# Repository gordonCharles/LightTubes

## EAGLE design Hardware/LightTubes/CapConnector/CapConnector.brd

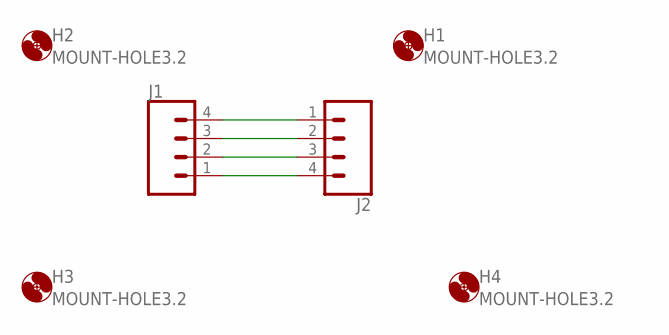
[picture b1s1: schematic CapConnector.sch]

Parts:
H1, H2, H3, H4: MOUNT-HOLE3.2; 3,2
J1: CONN_04POLAR; MOLEX-1X4
J2: CONN_04SMD_LONG; 1X04_SMD_LONG

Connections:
unnamed: J1.4, J2.1
unnamed: J1.3, J2.2
unnamed: J1.2, J2.3
unnamed: J1.1, J2.4

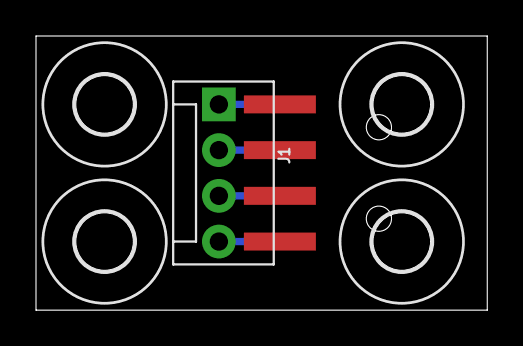
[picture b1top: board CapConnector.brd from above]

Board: 2 copper layers, 25.1 x 15.2 mm, 6 parts (0 on the bottom side), 4 nets.

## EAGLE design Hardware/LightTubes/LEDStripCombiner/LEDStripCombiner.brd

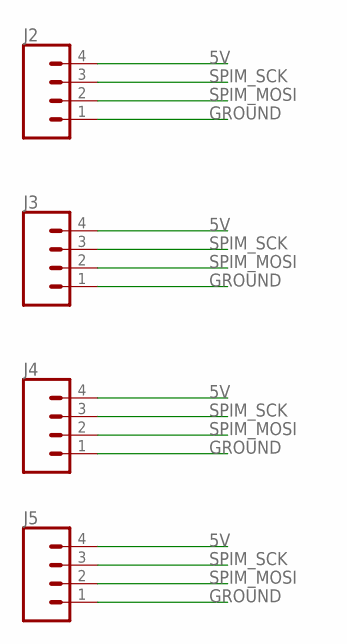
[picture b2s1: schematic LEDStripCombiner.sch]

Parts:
J2, J3, J4, J5: CONN_041X04_NO_SILK; 1X04_NO_SILK

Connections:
5V: J2.4, J3.4, J4.4, J5.4
GROUND: J2.1, J3.1, J4.1, J5.1
SPIM_MOSI: J2.2, J3.2, J4.2, J5.2
SPIM_SCK: J2.3, J3.3, J4.3, J5.3

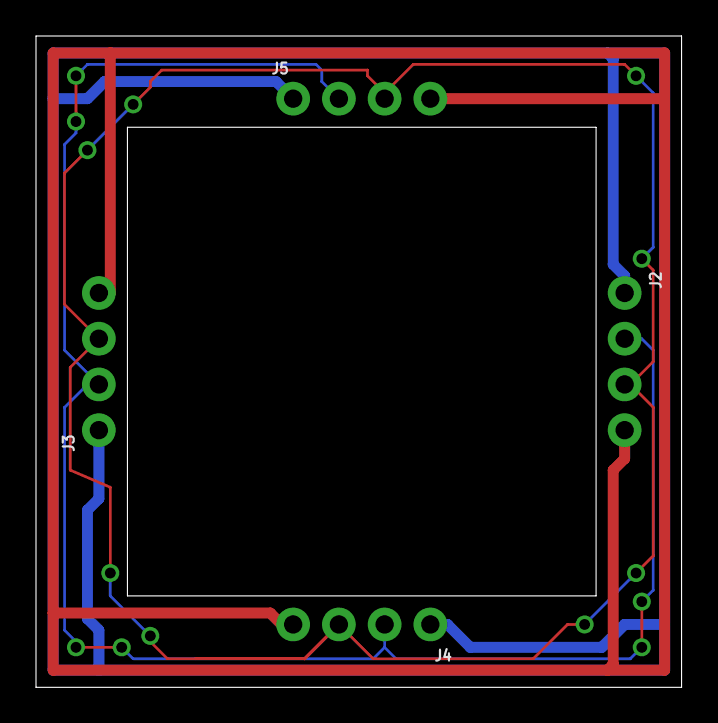
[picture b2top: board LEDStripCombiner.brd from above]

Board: 2 copper layers, 35.9 x 36.2 mm, 4 parts (0 on the bottom side), 4 nets.

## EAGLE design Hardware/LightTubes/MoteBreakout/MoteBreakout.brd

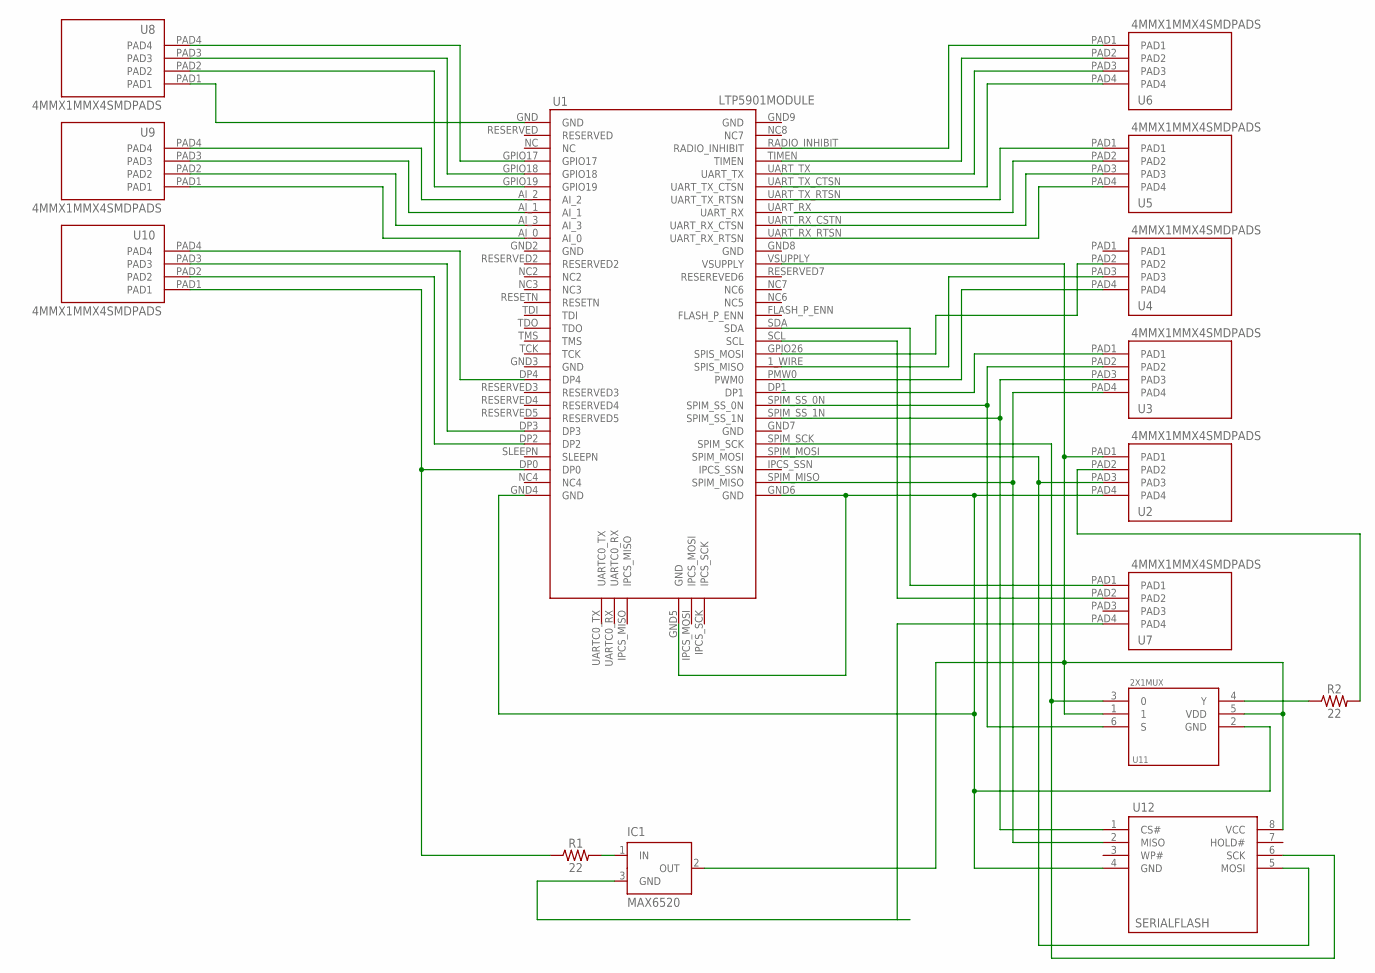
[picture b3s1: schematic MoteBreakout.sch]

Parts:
IC1: MAX6520; SOT23
R1, R2: 22; 0603
U1: LTP5901MODULE; LTP5901
U2, U3, U4, U5, U6, U7, U8, U9, U10: 4MMX1MMX4SMDPADS; 4MMX1MMX4SMD
U11: 2X1MUX; SOT457
U12: SERIALFLASH; 8S2

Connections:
GND: U1.GND2 (GND), U1.GND3 (GND), U1.GND7 (GND), U1.GND8 (GND), U1.GND9 (GND)
unnamed: U1.GND4 (GND), U1.GND5 (GND), U1.GND6 (GND), U2.PAD4, U11.2 (GND), U12.4 (GND)
unnamed: U1.SPIM_MOSI, U2.PAD3, U12.5 (MOSI)
unnamed: U1.SPIM_SCK, U11.3 (0), U12.6 (SCK)
unnamed: IC1.2 (OUT), U1.VSUPPLY, U2.PAD1, U11.1, U11.5 (VDD), U12.8 (VCC)
unnamed: U1.SPIM_MISO, U3.PAD4, U12.2 (MISO)
unnamed: U1.SPIM_SS_1N, U3.PAD3, U12.1 (CS#)
unnamed: U1.SPIM_SS_0N, U3.PAD2, U11.6 (S)
unnamed: U1.DP1, U3.PAD1
unnamed: U1.PMW0 (PWM0), U4.PAD4
unnamed: U1.1_WIRE (SPIS_MISO), U4.PAD3
unnamed: U1.GPIO26 (SPIS_MOSI), U4.PAD2
unnamed: U1.UART_RX_RTSN, U5.PAD4
unnamed: U1.UART_RX_CSTN (UART_RX_CTSN), U5.PAD3
unnamed: U1.UART_TX_RTSN, U5.PAD1
unnamed: U1.UART_TX_CTSN, U6.PAD4
unnamed: U1.UART_TX, U6.PAD3
unnamed: U1.TIMEN, U6.PAD2
unnamed: U1.RADIO_INHIBIT, U6.PAD1
unnamed: U1.GND, U8.PAD1
unnamed: U1.SDA, U7.PAD1
unnamed: U1.SCL, U7.PAD2
unnamed: IC1.3 (GND), U7.PAD4
unnamed: U1.GPIO17, U8.PAD4
unnamed: U1.GPIO18, U8.PAD3
unnamed: U1.GPIO19, U8.PAD2
unnamed: U1.AI_2, U9.PAD4
unnamed: U1.AI_1, U9.PAD3
unnamed: U1.AI_3, U9.PAD2
unnamed: U1.AI_0, U9.PAD1
unnamed: U1.DP4, U10.PAD4
unnamed: U1.DP3, U10.PAD3
unnamed: U1.DP2, U10.PAD2
unnamed: R1.1, U1.DP0, U10.PAD1
unnamed: R2.2, U2.PAD2
unnamed: R2.1, U11.4 (Y)
unnamed: IC1.1 (IN), R1.2

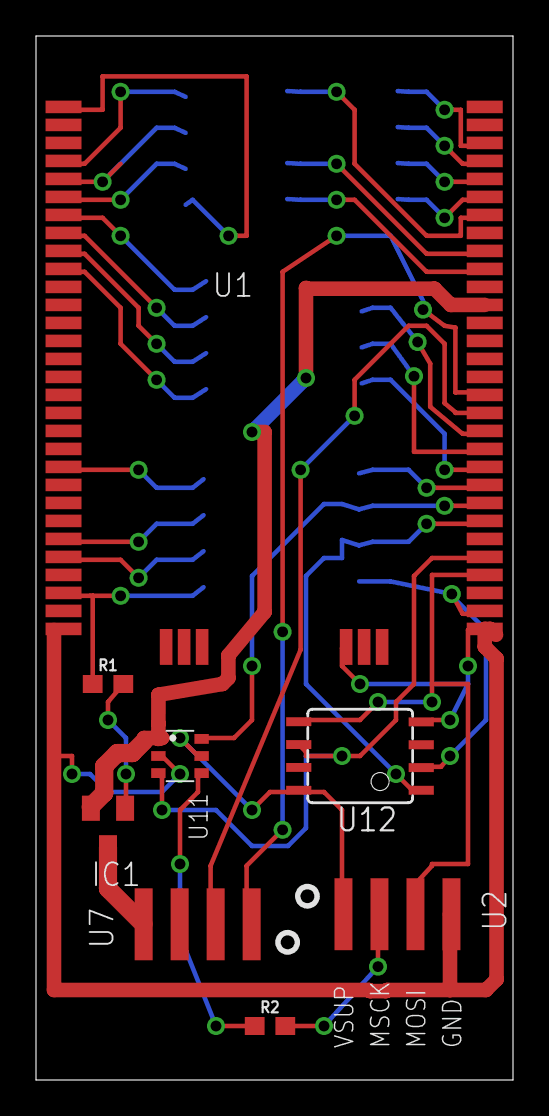
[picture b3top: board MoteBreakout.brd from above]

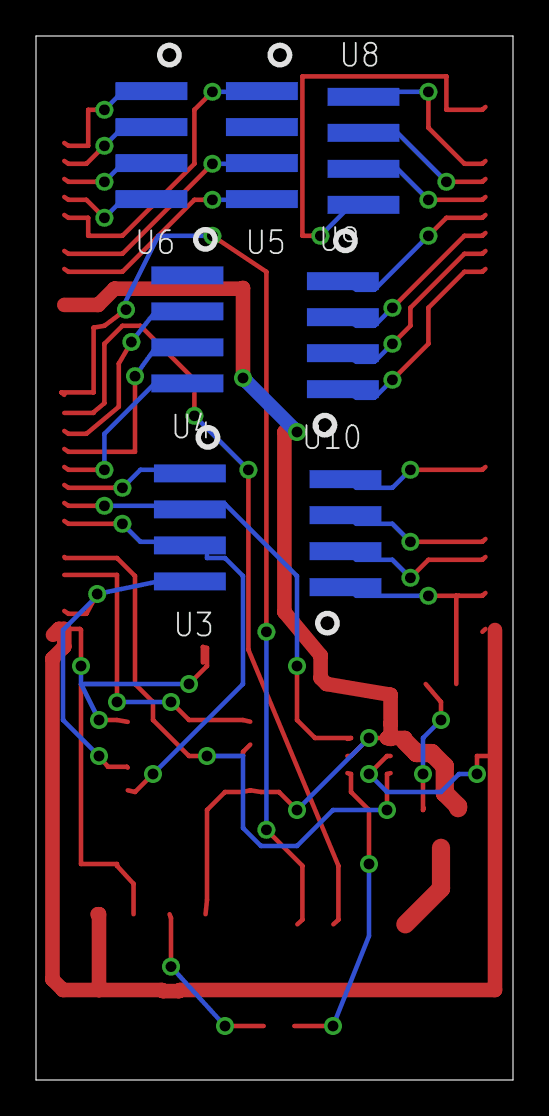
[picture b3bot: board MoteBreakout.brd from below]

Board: 2 copper layers, 26.5 x 58.0 mm, 15 parts (7 on the bottom side), 37 nets.

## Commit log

2020-12-21 Initial Checkin

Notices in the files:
parts and their libraries:
SparkFun-Connectors: Licensing: Creative Commons ShareAlike 4.0 International - https://creativecommons.org/licenses/by-sa/4.0
